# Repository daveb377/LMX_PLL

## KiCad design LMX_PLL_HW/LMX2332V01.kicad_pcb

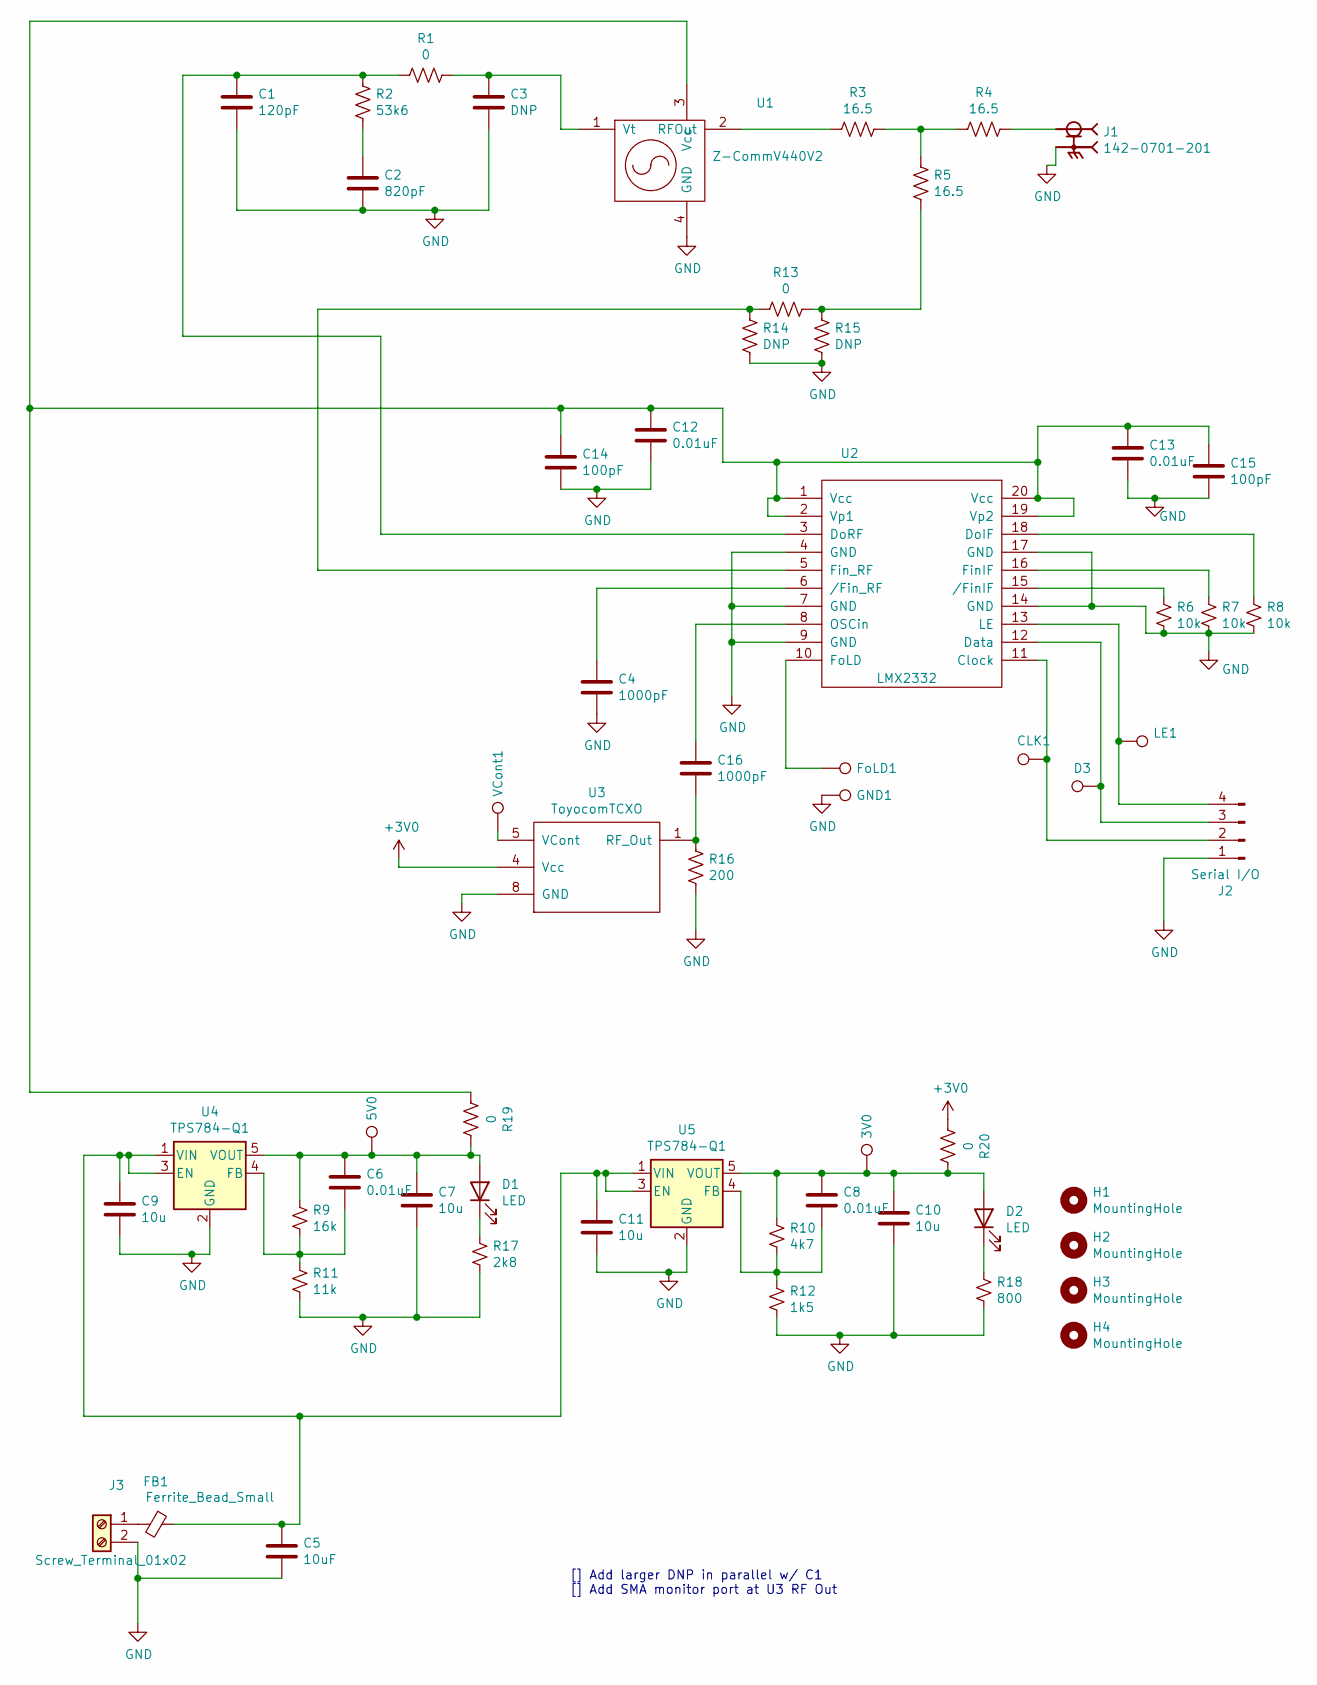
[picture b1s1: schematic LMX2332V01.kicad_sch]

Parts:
3V0, 5V0: TestPoint; TestPoint_THTPad_D2.0mm_Drill1.0mm
C1: 120pF; C_0805_2012Metric_Pad1.15x1.40mm_HandSolder
C2: 820pF; C_0805_HandSoldering
C3: DNP; C_0805_HandSoldering
C4, C16: 1000pF; C_0805_HandSoldering
C5: 10uF; C_0805_HandSoldering
C6, C8, C12, C13: 0.01uF; C_0805_HandSoldering
C7, C9, C10, C11: 10u; C_0805_HandSoldering
C14, C15: 100pF; C_0805_HandSoldering
CLK1: TestPoint; TestPoint_THTPad_D2.0mm_Drill1.0mm
D1, D2: LED; LED_0805_2012Metric
D3: TestPoint; TestPoint_THTPad_D2.0mm_Drill1.0mm
FB1: Ferrite_Bead_Small; C_0805_HandSoldering
FoLD1: TestPoint; TestPoint_THTPad_D2.0mm_Drill1.0mm
GND1: TestPoint; TestPoint_THTPad_D2.0mm_Drill1.0mm
H1, H2, H3, H4: MountingHole; MountingHole_3.2mm_M3_DIN965_Pad
J1: 142-0701-201; JOHNSON_142-0701-201
J2: Serial I/O; JST_PH_B4B-PH-K_1x04_P2.00mm_Vertical
J3: Screw_Terminal_01x02; TerminalBlock_TE_282834-2_1x02_P2.54mm_Horizontal
LE1: TestPoint; TestPoint_THTPad_D2.0mm_Drill1.0mm
R1, R13, R19, R20: 0; R_0805_HandSoldering
R2: 53k6; R_0805_HandSoldering
R3, R4, R5: 16.5; R_0805_HandSoldering
R6, R7, R8: 10k; R_0805_HandSoldering
R9: 16k; R_0805_HandSoldering
R10: 4k7; R_0805_HandSoldering
R11: 11k; R_0805_HandSoldering
R12: 1k5; R_0805_HandSoldering
R14, R15: DNP; R_0805_HandSoldering
R16: 200; R_0805_HandSoldering
R17: 2k8; R_0805_HandSoldering
R18: 800; R_0805_HandSoldering
U1: Z-CommV440V2; ZCommVCO
U2: LMX2332; TSSOP-20_4.4x6.5mm_Pitch0.65mm
U3: ToyocomTCXO
U4, U5: TPS784-Q1; SOT-23-5
VCont1: TestPoint; TestPoint_THTPad_D2.0mm_Drill1.0mm

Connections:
+3V0: R20.2, U3.4 (Vcc)
GND: C1.2, C2.2, C3.2, C4.2, C5.2, C7.2, C9.2, C10.2, C11.2, C12.2, C13.2, C14.2, C15.2, GND1.1, J1.2, J1.3, J1.4, J1.5, J2.1, J3.2, R6.2, R7.2, R8.2, R11.2, R12.2, R14.2, R15.2, R16.2, R17.2, R18.2, U1.4 (GND), U2.4 (GND), U2.7 (GND), U2.9 (GND), U2.14 (GND), U2.17 (GND), U3.8 (GND), U4.2 (GND), U5.2 (GND)
unnamed: 3V0.1, C8.1, C10.1, D2.2 (A), R10.1, R20.1, U5.5 (VOUT)
unnamed: 5V0.1, C6.1, C7.1, D1.2 (A), R9.1, R19.1, U4.5 (VOUT)
unnamed: C1.1, R1.2, R2.1, U2.3 (DoRF)
unnamed: C2.1, R2.2
unnamed: C3.1, R1.1, U1.1 (Vt)
unnamed: C4.1, U2.6 (/Fin_RF)
unnamed: C6.2, R9.2, R11.1, U4.4 (FB)
unnamed: C8.2, R10.2, R12.1, U5.4 (FB)
unnamed: C5.1, C9.1, C11.1, FB1.1, U4.1 (VIN), U4.3 (EN), U5.1 (VIN), U5.3 (EN)
unnamed: C12.1, C13.1, C14.1, C15.1, R19.2, U1.3 (Vcc), U2.1 (Vcc), U2.2 (Vp1), U2.19 (Vp2), U2.20 (Vcc)
unnamed: C16.1, U2.8 (OSCin)
unnamed: C16.2, R16.1, U3.1 (RF_Out)
unnamed: CLK1.1, J2.2, U2.11 (Clock)
unnamed: D1.1 (K), R17.1
unnamed: D2.1 (K), R18.1
unnamed: D3.1, J2.3, U2.12 (Data)
unnamed: FB1.2, J3.1
unnamed: FoLD1.1, U2.10 (FoLD)
unnamed: J1.1, R4.1
unnamed: J2.4, LE1.1, U2.13 (LE)
unnamed: R3.1, R4.2, R5.1
unnamed: R3.2, U1.2 (RFOut)
unnamed: R6.1, U2.15 (/FinIF)
unnamed: R7.1, U2.16 (FinIF)
unnamed: R8.1, U2.18 (DoIF)
unnamed: R5.2, R13.1, R15.1
unnamed: R13.2, R14.1, U2.5 (Fin_RF)
unnamed: U3.5 (VCont), VCont1.1

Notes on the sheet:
[] Add larger DNP in parallel w/ C1 [] Add SMA monitor port at U3 RF Out

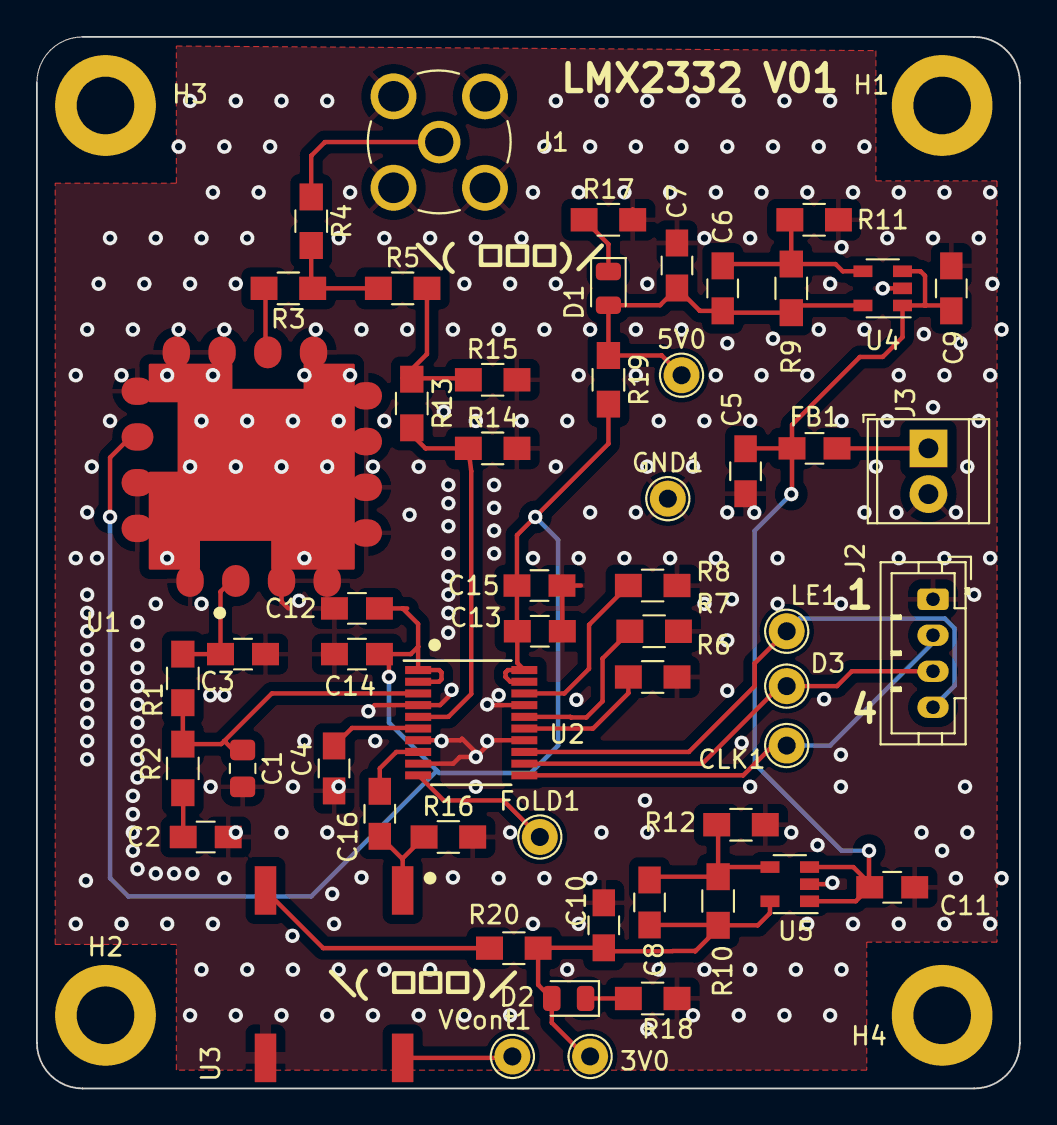
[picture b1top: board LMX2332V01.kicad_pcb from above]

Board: 2 copper layers, 54.6 x 58.4 mm, 59 parts (0 on the bottom side), 30 nets.

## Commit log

2021-07-02 Added Schematic PDF
2021-07-06 Update 2021-07-05
    Finished Schematic enough to get a first cut pulled into the layout.
    Also finished PLL_Calculations.py enought to get loop filter component footprints nailed. Still needs more work, but ongoing. I'm using Spyder as a Python IDE.
2021-07-09 Layout Updates
    Almost OK.
2021-08-25 PCB Layout Updates. Not completed yet
2022-01-03 As sent out to OshPark. Using KiCad 6.0.
    As sent out to OshPark. Using KiCad 6.0.
2022-01-27 As Built including Gerbers
    As Built including Gerbers
2022-02-06 Added an interactive BOM
2023-06-23 Update 2023-06-22
    Cleanup
2023-06-23 Delete LMX_PLL_HW/LMX2332V01-backups directory
    Deleted all of the Kicad Backups
